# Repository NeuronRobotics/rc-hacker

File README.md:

# rc-hacker

The RC Hacker combines the ESP8266 with 2 H bridges and
a MONO audio DAC/AMP and 5 GPIO. It is Programmed over
WIFI and is intended to be used to "Upcycle" old toys and
turn them into programable robots.

- ESP8266-12 wifi module
- Dual L9110 (800ma) DACs
- ALC5628 DAC+AMP
- Screw Terminals to attatch motors
- 5x 0.1" 3 pin headers for additional sensors/servos and 1 analog in.

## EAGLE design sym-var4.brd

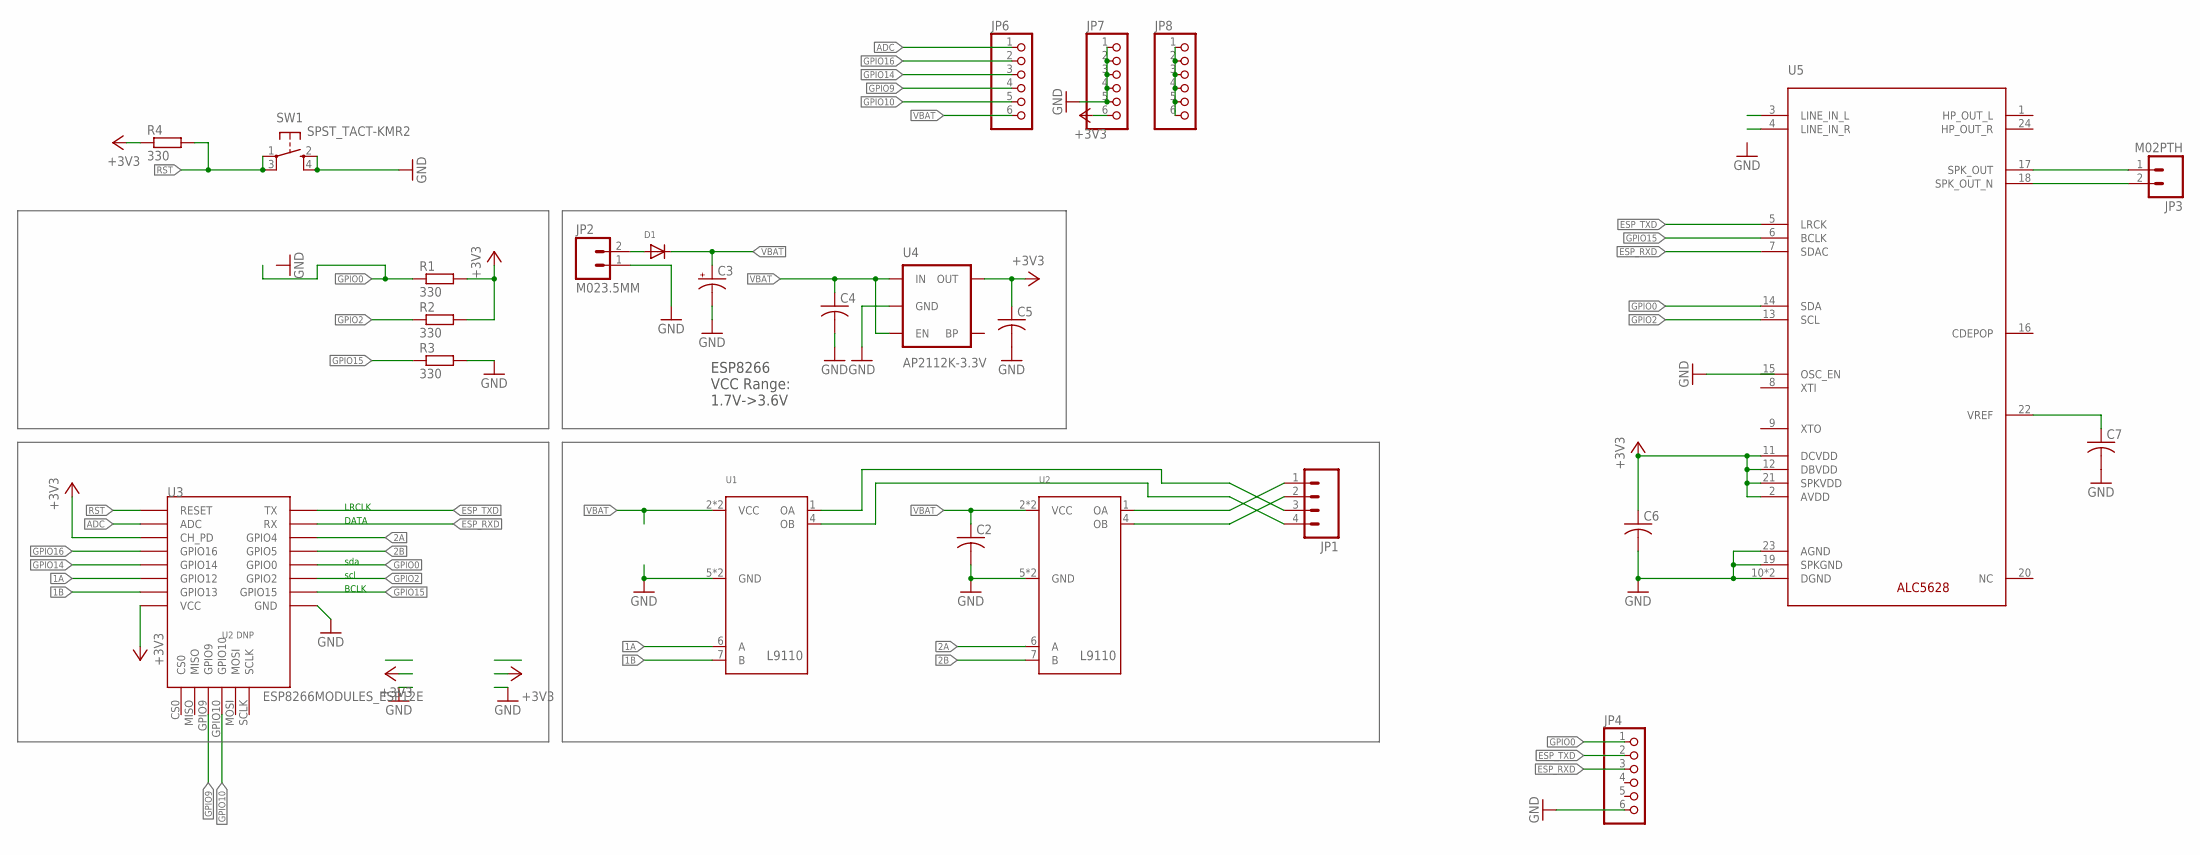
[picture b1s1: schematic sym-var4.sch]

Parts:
C2, C4, C5, C6, C7: C-USC0805; C0805
C3: CPOL-USE2-5; E2-5
D1: DIODESMA; SMADIODE
JP1: M04SCREW; SCREWTERMINAL-3.5MM-4
JP2: M023.5MM; SCREWTERMINAL-3.5MM-2
JP3: M02PTH; 1X02
JP4, JP6, JP7, JP8: PINHD-1X6; 1X06
R1, R2, R3, R4: 330; R0805
SW1: SPST_TACT-KMR2; KMR2
U1, U2: L9110; DIP8
U3: ESP8266MODULES_ESP12E
U4: AP2112K-3.3V; SOT23-5
U5: ALC5628; QFN24

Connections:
1A: U1.6 (A), U3.GPIO12
1B: U1.7 (B), U3.GPIO_13 (GPIO13)
2A: U2.6 (A), U3.GPIO4
2B: U2.7 (B), U3.GPIO5
+3V3: C5.1, C6.1, JP7.6, R1.2, R2.2, R4.1, U3.CH_PD, U3.VCC, U4.5 (OUT), U5.2 (AVDD), U5.11 (DCVDD), U5.12 (DBVDD), U5.21 (SPKVDD)
ADC: JP6.1, U3.ADC
ESP_RXD: JP4.3, U3.RX, U5.7 (SDAC)
ESP_TXD: JP4.2, U3.TX, U5.5 (LRCK)
GND: C2.2, C3.-, C4.2, C5.2, C6.2, C7.2, JP2.1, JP4.6, JP7.1, JP7.2, JP7.3, JP7.4, JP7.5, R3.2, SW1.2 (S), SW1.4 (S1), U1.5 (GND), U1.8 (GND), U2.5 (GND), U2.8 (GND), U3.GND, U4.2 (GND), U5.10 (DGND), U5.19 (SPKGND), U5.23 (AGND), U5.PAD (DGND)
GPIO0: JP4.1, R1.1, U3.GPIO0, U5.14 (SDA)
GPIO2: R2.1, U3.GPIO2, U5.13 (SCL)
GPIO9: JP6.4, U3.GPIO9
GPIO10: JP6.5, U3.GPIO10
GPIO14: JP6.3, U3.GPIO14
GPIO15: R3.1, U3.GPIO15, U5.6 (BCLK)
GPIO16: JP6.2, U3.GPIO_16 (GPIO16)
unnamed: JP1.1, U2.1 (OA)
unnamed: JP1.2, U2.4 (OB)
unnamed: JP1.4, U1.4 (OB)
unnamed: JP1.3, U1.1 (OA)
unnamed: D1.A, JP2.2
unnamed: C7.1, U5.22 (VREF)
unnamed: JP8.1, JP8.2, JP8.3, JP8.4, JP8.5, JP8.6
unnamed: JP3.1, U5.17 (SPK_OUT)
unnamed: JP3.2, U5.18 (SPK_OUT_N)
RST: R4.2, SW1.1, SW1.3 (P1), U3.RESET
VBAT: C2.1, C3.+, C4.1, D1.C, JP6.6, U1.2 (VCC), U1.3 (VCC), U2.2 (VCC), U2.3 (VCC), U4.1 (IN), U4.3 (EN)

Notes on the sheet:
U2 DNP
ESP8266 VCC Range: 1.7V->3.6V
LRCLK
DATA
BCLK
sda
scl

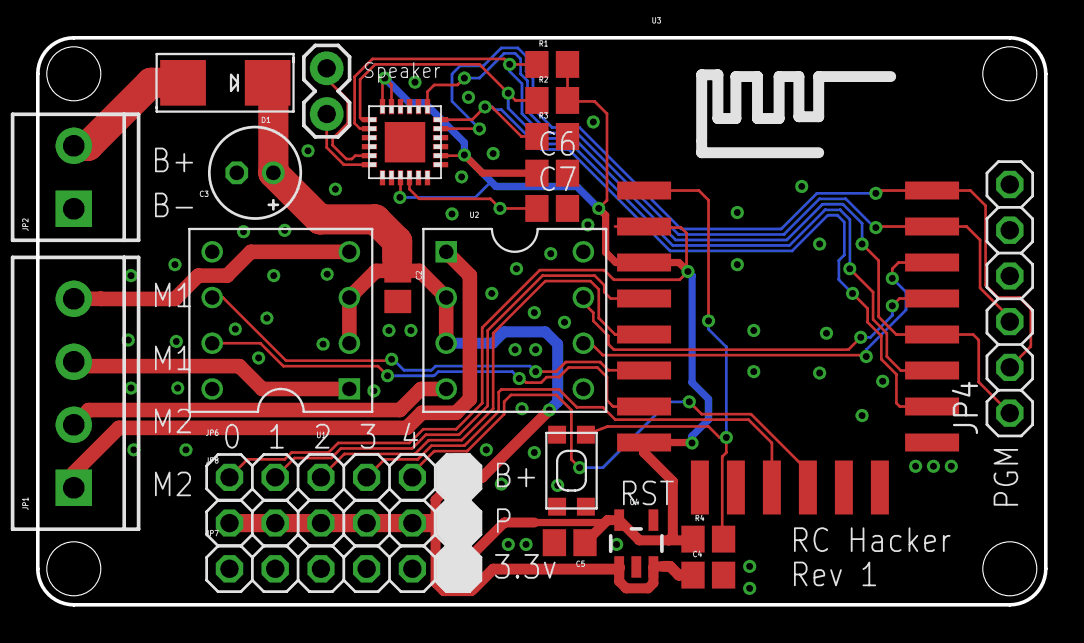
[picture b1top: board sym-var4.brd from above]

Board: 2 copper layers, 56.0 x 31.5 mm, 24 parts (0 on the bottom side), 27 nets.

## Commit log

2016-01-17 Added PCB
2016-01-17 Added Prog Connector
2016-01-17 Added Board IMG
2016-01-18 Layout complete
2016-01-18 Updated image
2016-01-25 Added logo

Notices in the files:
parts and their libraries:
SparkFun-Connectors: Licensing: Creative Commons ShareAlike 4.0 International - https://creativecommons.org/licenses/by-sa/4.0
